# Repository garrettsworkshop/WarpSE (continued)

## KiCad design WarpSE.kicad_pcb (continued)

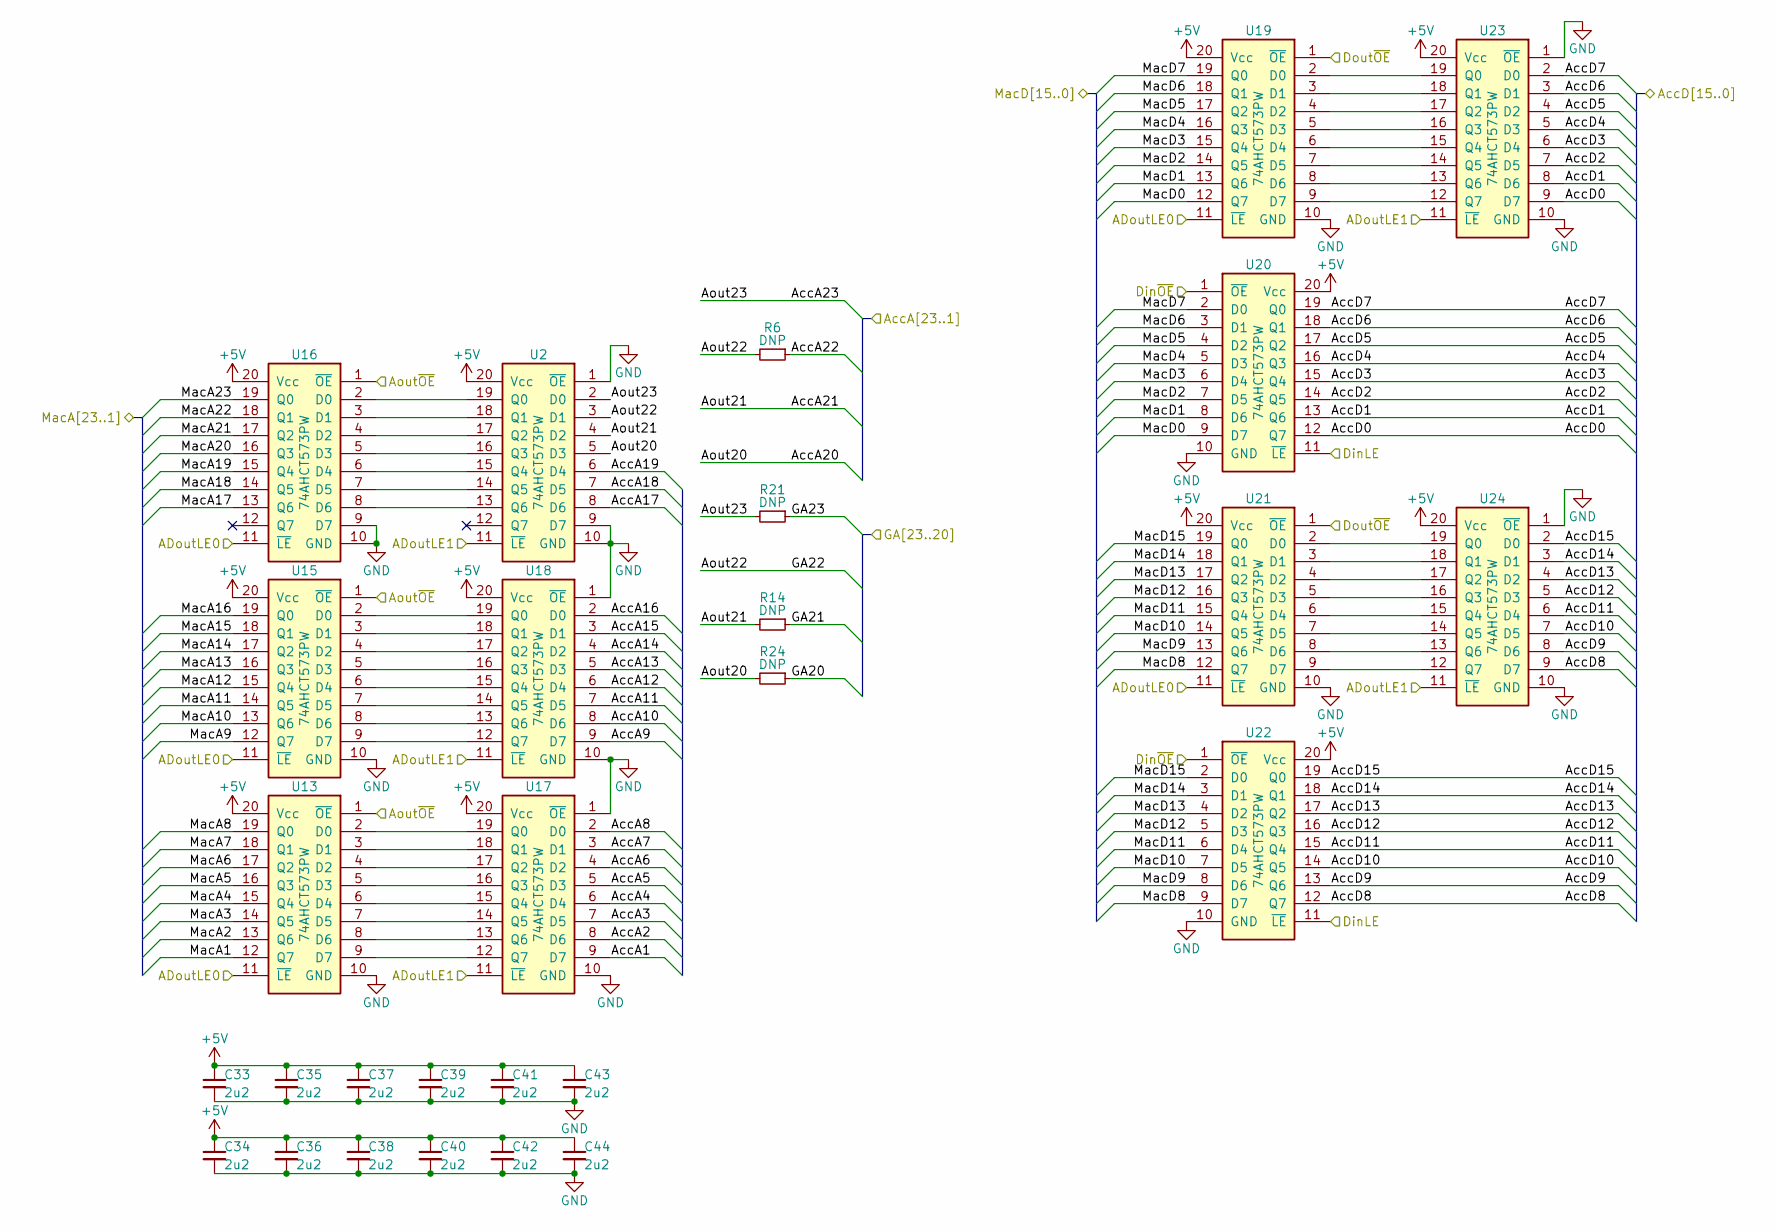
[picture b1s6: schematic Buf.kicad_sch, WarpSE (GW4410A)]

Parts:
C33, C34, C35, C36, C37, C38, C39, C40, C41, C42, C43, C44: 2u2; C_0603; LCSC Part C23630
R6, R14, R21, R24: DNP; R_0603
U2, U13, U15, U16, U17, U18, U19, U20, U21, U22, U23, U24: 74AHCT573PW; TSSOP-20_4.4x6.5mm_P0.65mm; LCSC Part C141311

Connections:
+5V: C33.1, C34.1, C35.1, C36.1, C37.1, C38.1, C39.1, C40.1, C41.1, C42.1, C43.1, C44.1, U2.20 (Vcc), U13.20 (Vcc), U15.20 (Vcc), U16.20 (Vcc), U17.20 (Vcc), U18.20 (Vcc), U19.20 (Vcc), U20.20 (Vcc), U21.20 (Vcc), U22.20 (Vcc), U23.20 (Vcc), U24.20 (Vcc); also elsewhere on the board
/Buf/ADoutLE0: U13.11 (~LE), U15.11 (~LE), U16.11 (~LE), U19.11 (~LE), U21.11 (~LE); also elsewhere on the board
/Buf/ADoutLE1: U2.11 (~LE), U17.11 (~LE), U18.11 (~LE), U23.11 (~LE), U24.11 (~LE); also elsewhere on the board
/Buf/AccA1: U17.9 (D7); also elsewhere on the board
/Buf/AccA2: U17.8 (D6); also elsewhere on the board
/Buf/AccA3: U17.7 (D5); also elsewhere on the board
/Buf/AccA4: U17.6 (D4); also elsewhere on the board
/Buf/AccA5: U17.5 (D3); also elsewhere on the board
/Buf/AccA6: U17.4 (D2); also elsewhere on the board
/Buf/AccA7: U17.3 (D1); also elsewhere on the board
/Buf/AccA8: U17.2 (D0); also elsewhere on the board
/Buf/AccA9: U18.9 (D7); also elsewhere on the board
/Buf/AccA10: U18.8 (D6); also elsewhere on the board
/Buf/AccA11: U18.7 (D5); also elsewhere on the board
/Buf/AccA12: U18.6 (D4); also elsewhere on the board
/Buf/AccA13: U18.5 (D3); also elsewhere on the board
/Buf/AccA14: U18.4 (D2); also elsewhere on the board
/Buf/AccA15: U18.3 (D1); also elsewhere on the board
/Buf/AccA16: U18.2 (D0); also elsewhere on the board
/Buf/AccA17: U2.8 (D6); also elsewhere on the board
/Buf/AccA18: U2.7 (D5); also elsewhere on the board
/Buf/AccA19: U2.6 (D4); also elsewhere on the board
/Buf/AccA20: R24.2, U2.5 (D3); also elsewhere on the board
/Buf/AccA21: R14.2, U2.4 (D2); also elsewhere on the board
/Buf/AccA22: R6.1; also elsewhere on the board
/Buf/AccA23: R21.2, U2.2 (D0); also elsewhere on the board
/Buf/AccD0: U20.12 (Q7), U23.9 (D7); also elsewhere on the board
/Buf/AccD1: U20.13 (Q6), U23.8 (D6); also elsewhere on the board
/Buf/AccD2: U20.14 (Q5), U23.7 (D5); also elsewhere on the board
/Buf/AccD3: U20.15 (Q4), U23.6 (D4); also elsewhere on the board
/Buf/AccD4: U20.16 (Q3), U23.5 (D3); also elsewhere on the board
/Buf/AccD5: U20.17 (Q2), U23.4 (D2); also elsewhere on the board
/Buf/AccD6: U20.18 (Q1), U23.3 (D1); also elsewhere on the board
/Buf/AccD7: U20.19 (Q0), U23.2 (D0); also elsewhere on the board
/Buf/AccD8: U22.12 (Q7), U24.9 (D7); also elsewhere on the board
/Buf/AccD9: U22.13 (Q6), U24.8 (D6); also elsewhere on the board
/Buf/AccD10: U22.14 (Q5), U24.7 (D5); also elsewhere on the board
/Buf/AccD11: U22.15 (Q4), U24.6 (D4); also elsewhere on the board
/Buf/AccD12: U22.16 (Q3), U24.5 (D3); also elsewhere on the board
/Buf/AccD13: U22.17 (Q2), U24.4 (D2); also elsewhere on the board
/Buf/AccD14: U22.18 (Q1), U24.3 (D1); also elsewhere on the board
/Buf/AccD15: U22.19 (Q0), U24.2 (D0); also elsewhere on the board
/Buf/Aout~OE: U13.1 (~OE), U15.1 (~OE), U16.1 (~OE); also elsewhere on the board
/Buf/DinLE: U20.11 (~LE), U22.11 (~LE); also elsewhere on the board
/Buf/Din~OE: U20.1 (~OE), U22.1 (~OE); also elsewhere on the board
/Buf/Dout~OE: U19.1 (~OE), U21.1 (~OE); also elsewhere on the board
/Buf/GA20: R24.1; also elsewhere on the board
/Buf/GA21: R14.1; also elsewhere on the board
/Buf/GA22: R6.2, U2.3 (D1); also elsewhere on the board
/Buf/GA23: R21.1; also elsewhere on the board
/Buf/MacA1: U13.12 (Q7); also elsewhere on the board
/Buf/MacA2: U13.13 (Q6); also elsewhere on the board
/Buf/MacA3: U13.14 (Q5); also elsewhere on the board
/Buf/MacA4: U13.15 (Q4); also elsewhere on the board
/Buf/MacA5: U13.16 (Q3); also elsewhere on the board
/Buf/MacA6: U13.17 (Q2); also elsewhere on the board
/Buf/MacA7: U13.18 (Q1); also elsewhere on the board
/Buf/MacA8: U13.19 (Q0); also elsewhere on the board
/Buf/MacA9: U15.12 (Q7); also elsewhere on the board
/Buf/MacA10: U15.13 (Q6); also elsewhere on the board
/Buf/MacA11: U15.14 (Q5); also elsewhere on the board
/Buf/MacA12: U15.15 (Q4); also elsewhere on the board
/Buf/MacA13: U15.16 (Q3); also elsewhere on the board
/Buf/MacA14: U15.17 (Q2); also elsewhere on the board
/Buf/MacA15: U15.18 (Q1); also elsewhere on the board
/Buf/MacA16: U15.19 (Q0); also elsewhere on the board
/Buf/MacA17: U16.13 (Q6); also elsewhere on the board
/Buf/MacA18: U16.14 (Q5); also elsewhere on the board
/Buf/MacA19: U16.15 (Q4); also elsewhere on the board
/Buf/MacA20: U16.16 (Q3); also elsewhere on the board
/Buf/MacA21: U16.17 (Q2); also elsewhere on the board
/Buf/MacA22: U16.18 (Q1); also elsewhere on the board
/Buf/MacA23: U16.19 (Q0); also elsewhere on the board
/Buf/MacD0: U19.12 (Q7), U20.9 (D7); also elsewhere on the board
/Buf/MacD1: U19.13 (Q6), U20.8 (D6); also elsewhere on the board
/Buf/MacD2: U19.14 (Q5), U20.7 (D5); also elsewhere on the board
/Buf/MacD3: U19.15 (Q4), U20.6 (D4); also elsewhere on the board
/Buf/MacD4: U19.16 (Q3), U20.5 (D3); also elsewhere on the board
/Buf/MacD5: U19.17 (Q2), U20.4 (D2); also elsewhere on the board
/Buf/MacD6: U19.18 (Q1), U20.3 (D1); also elsewhere on the board
/Buf/MacD7: U19.19 (Q0), U20.2 (D0); also elsewhere on the board
/Buf/MacD8: U21.12 (Q7), U22.9 (D7); also elsewhere on the board
/Buf/MacD9: U21.13 (Q6), U22.8 (D6); also elsewhere on the board
/Buf/MacD10: U21.14 (Q5), U22.7 (D5); also elsewhere on the board
/Buf/MacD11: U21.15 (Q4), U22.6 (D4); also elsewhere on the board
/Buf/MacD12: U21.16 (Q3), U22.5 (D3); also elsewhere on the board
/Buf/MacD13: U21.17 (Q2), U22.4 (D2); also elsewhere on the board
/Buf/MacD14: U21.18 (Q1), U22.3 (D1); also elsewhere on the board
/Buf/MacD15: U21.19 (Q0), U22.2 (D0); also elsewhere on the board
GND: C33.2, C34.2, C35.2, C36.2, C37.2, C38.2, C39.2, C40.2, C41.2, C42.2, C43.2, C44.2, U2.1 (~OE), U2.9 (D7), U2.10 (GND), U13.10 (GND), U15.10 (GND), U16.9 (D7), U16.10 (GND), U17.1 (~OE), U17.10 (GND), U18.1 (~OE), U18.10 (GND), U19.10 (GND), U20.10 (GND), U21.10 (GND), U22.10 (GND), U23.1 (~OE), U23.10 (GND), U24.1 (~OE), U24.10 (GND); also elsewhere on the board
unnamed: U13.2 (D0), U17.19 (Q0)
unnamed: U13.3 (D1), U17.18 (Q1)
unnamed: U13.4 (D2), U17.17 (Q2)
unnamed: U13.5 (D3), U17.16 (Q3)
unnamed: U13.6 (D4), U17.15 (Q4)
unnamed: U13.7 (D5), U17.14 (Q5)
unnamed: U13.8 (D6), U17.13 (Q6)
unnamed: U13.9 (D7), U17.12 (Q7)
unnamed: U15.2 (D0), U18.19 (Q0)
unnamed: U15.3 (D1), U18.18 (Q1)
unnamed: U15.4 (D2), U18.17 (Q2)
unnamed: U15.5 (D3), U18.16 (Q3)
unnamed: U15.6 (D4), U18.15 (Q4)
unnamed: U15.7 (D5), U18.14 (Q5)
unnamed: U15.8 (D6), U18.13 (Q6)
unnamed: U15.9 (D7), U18.12 (Q7)
unnamed: U2.19 (Q0), U16.2 (D0)
unnamed: U2.18 (Q1), U16.3 (D1)
unnamed: U2.17 (Q2), U16.4 (D2)
unnamed: U2.16 (Q3), U16.5 (D3)
unnamed: U2.15 (Q4), U16.6 (D4)
unnamed: U2.14 (Q5), U16.7 (D5)
unnamed: U2.13 (Q6), U16.8 (D6)
unnamed: U19.2 (D0), U23.19 (Q0)
unnamed: U19.3 (D1), U23.18 (Q1)
unnamed: U19.4 (D2), U23.17 (Q2)
unnamed: U19.5 (D3), U23.16 (Q3)
unnamed: U19.6 (D4), U23.15 (Q4)
unnamed: U19.7 (D5), U23.14 (Q5)
unnamed: U19.8 (D6), U23.13 (Q6)
unnamed: U19.9 (D7), U23.12 (Q7)
unnamed: U21.2 (D0), U24.19 (Q0)
unnamed: U21.3 (D1), U24.18 (Q1)
unnamed: U21.4 (D2), U24.17 (Q2)
unnamed: U21.5 (D3), U24.16 (Q3)
unnamed: U21.6 (D4), U24.15 (Q4)
unnamed: U21.7 (D5), U24.14 (Q5)
unnamed: U21.8 (D6), U24.13 (Q6)
unnamed: U21.9 (D7), U24.12 (Q7)

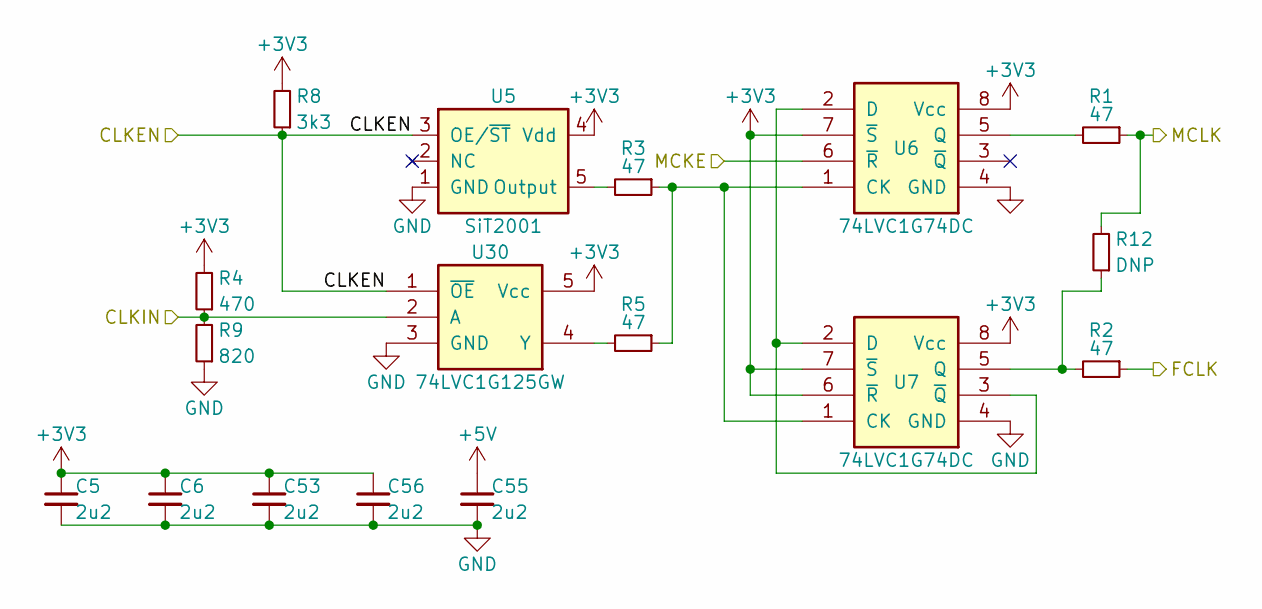
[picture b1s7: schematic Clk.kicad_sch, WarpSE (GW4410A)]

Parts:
C5, C6, C53, C55, C56: 2u2; C_0603; LCSC Part C23630
R1, R2, R3, R5: 47; R_0603; LCSC Part C23182
R4: 470; R_0603; LCSC Part C21190
R8: 3k3; R_0603; LCSC Part C21190
R9: 820; R_0603; LCSC Part C21190
R12: DNP; R_0603
U5: SiT2001; SOT-23-5; LCSC Part C17253174
U6, U7: 74LVC1G74DC; NXP_VSSOP-8_2.3x2mm; LCSC Part C503431
U30: 74LVC1G125GW; SOT-353; LCSC Part C12519

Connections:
+3V3: C5.1, C6.1, C53.1, C56.1, R4.2, R8.2, U5.4 (Vdd), U6.7 (~S), U6.8 (Vcc), U7.6 (~R), U7.7 (~S), U7.8 (Vcc), U30.5 (Vcc); also elsewhere on the board
+5V: C55.1; also elsewhere on the board
/Clk.sch/CLKEN: R8.1, U5.3 (OE/~ST), U30.1 (~OE); also elsewhere on the board
/Clk.sch/CLKIN: R4.1, R9.2, U30.2 (A); also elsewhere on the board
/Clk.sch/FCLK: R2.1; also elsewhere on the board
/Clk.sch/MCKE: U6.6 (~R); also elsewhere on the board
/Clk.sch/MCLK: R1.1, R12.2; also elsewhere on the board
GND: C5.2, C6.2, C53.2, C55.2, C56.2, R9.1, U5.1 (GND), U6.4 (GND), U7.4 (GND), U30.3 (GND); also elsewhere on the board
unnamed: R3.2, U5.5 (Output)
unnamed: R3.1, R5.1, U6.1 (CK), U7.1 (CK)
unnamed: U6.2 (D), U7.2 (D), U7.3 (~Q)
unnamed: R1.2, U6.5 (Q)
unnamed: R2.2, R12.1, U7.5 (Q)
unnamed: R5.2, U30.4 (Y)

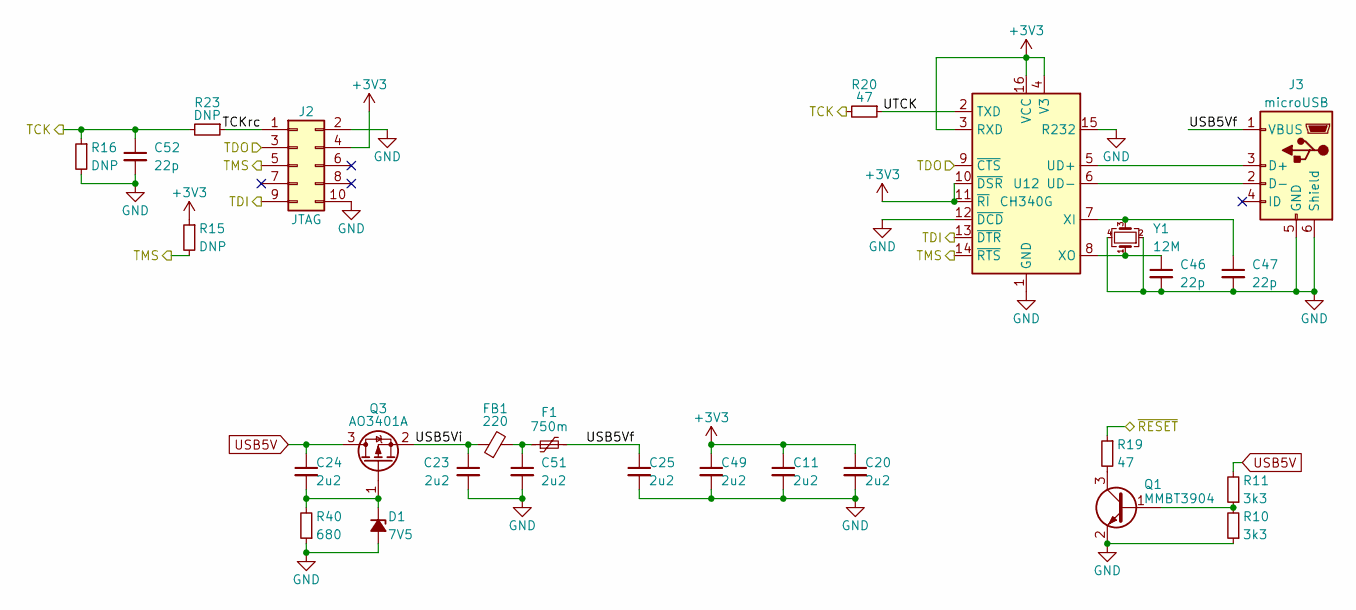
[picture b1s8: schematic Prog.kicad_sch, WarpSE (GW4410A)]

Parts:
C11, C20, C23, C24, C25, C49, C51: 2u2; C_0603; LCSC Part C23630
C46, C47, C52: 22p; C_0603; LCSC Part C1653
D1: 7V5; D_SOD-323; LCSC Part C95638
F1: 750m; BelFuse_1206; LCSC Part C126818
FB1: 220; C_0805; LCSC Part C85840
J2: JTAG; Tag-Connect_TC2050-IDC-FP_2x05_P1.27mm_Vertical
J3: microUSB; USB_Micro-B_Amphenol_10118192-0001; LCSC Part C132564
Q1: MMBT3904; SOT-23; LCSC Part C20526
Q3: AO3401A; SOT-23
R10, R11: 3k3; R_0603; LCSC Part C21190
R15, R16, R23: DNP; R_0603
R19, R20: 47; R_0603; LCSC Part C23182
R40: 680; R_0805; LCSC Part C17798
U12: CH340G; SOIC-16_3.9mm; LCSC Part C14267
Y1: 12M; Crystal_SMD_3225-4Pin_3.2x2.5mm; LCSC Part C9002

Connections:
+3V3: C11.1, C20.1, C49.1, J2.4, R15.1, U12.3 (RXD), U12.4 (V3), U12.10 (~DSR), U12.11 (~RI), U12.16 (VCC); also elsewhere on the board
/Control/TCK: C52.1, R16.1, R20.2, R23.2; also elsewhere on the board
/Control/TDI: J2.9, U12.13 (~DTR); also elsewhere on the board
/Control/TDO: J2.3, U12.9 (~CTS); also elsewhere on the board
/Control/TMS: J2.5, R15.2, U12.14 (~RTS); also elsewhere on the board
/Control/~RESET: R19.1; also elsewhere on the board
/Prog/TCKrc: J2.1, R23.1
/Prog/USB5Vf: C25.1, F1.2, J3.1 (VBUS)
/Prog/USB5Vi: C23.1, FB1.1, Q3.2 (S)
/Prog/UTCK: R20.1, U12.2 (TXD)
GND: C11.2, C20.2, C23.2, C25.2, C46.2, C47.2, C49.2, C51.2, C52.2, D1.2 (A), J2.2, J2.10, J3.5 (GND), J3.6 (Shield), Q1.2 (E), R10.1, R16.2, R40.1, U12.1 (GND), U12.12 (~DCD), U12.15 (R232), Y1.2, Y1.4; also elsewhere on the board
unnamed: C51.1, F1.1, FB1.2
unnamed: C24.2, D1.1 (K), Q3.1 (G), R40.2
unnamed: J3.3 (D+), U12.5 (UD+)
unnamed: J3.2 (D-), U12.6 (UD-)
unnamed: Q1.1 (B), R10.2, R11.1
unnamed: Q1.3 (C), R19.2
unnamed: C47.1, U12.7 (XI), Y1.3
unnamed: C46.1, U12.8 (XO), Y1.1
USB5V: C24.1, Q3.3 (D), R11.2; also elsewhere on the board

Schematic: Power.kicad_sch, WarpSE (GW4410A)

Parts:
C3, C4, C7, C8, C9, C10: 10u; C_0805; LCSC Part C15850
C19, C45, C50: 2u2; C_0603; LCSC Part C23630
Q2: DNP; SOT-23
R25, R26, R27: 680; R_0805; LCSC Part C17798
R28: DNP; R_0805
R37: 3k3; R_0603; LCSC Part C21190
U3: AZ1117CH-3.3TRG1; SOT-223; LCSC Part C92102
U4, U25: LM66100DCK; SOT-363; LCSC Part C2869734

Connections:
+3V3: C7.1, C8.1, C9.1, C10.1, R26.1, R28.1, U3.2 (VO); also elsewhere on the board
+5V: C3.1, C4.1, C19.1, C45.1, Q2.2 (E), R25.1, U3.3 (VI), U4.6 (Vout), U25.6 (Vout); also elsewhere on the board
+5Vin: R27.1, R37.2, U25.1 (Vin); also elsewhere on the board
GND: C3.2, C4.2, C7.2, C8.2, C9.2, C10.2, C19.2, C45.2, C50.2, R25.2, R26.2, R27.2, U3.1 (GND), U4.2 (GND), U25.2 (GND); also elsewhere on the board
unnamed: Q2.1 (B), Q2.3 (C), R28.2
unnamed: R37.1, U4.3 (~CE), U25.5 (ST)
USB5V: C50.1, U4.1 (Vin), U25.3 (~CE); also elsewhere on the board

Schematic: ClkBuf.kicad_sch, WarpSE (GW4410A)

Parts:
C21, C48, C54: 2u2; C_0603; LCSC Part C23630
R7, R17, R18: 47; R_0603; LCSC Part C23182
R29: 22k; R_0805; LCSC Part C17560
U26, U27, U28: 74LVC1G32GW; SOT-353; LCSC Part C12516

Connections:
+3V3: C21.1, C48.1, C54.1, U26.5 (Vcc), U27.5 (Vcc), U28.5 (Vcc); also elsewhere on the board
+5Vin: R29.1; also elsewhere on the board
/ClkBuf/BC8M: R17.1; also elsewhere on the board
/ClkBuf/BC16M: R7.1; also elsewhere on the board
/ClkBuf/BE: R18.1; also elsewhere on the board
/ClkBuf/C8M: R29.2, U27.2 (B); also elsewhere on the board
/ClkBuf/C16M: U28.2 (B); also elsewhere on the board
/ClkBuf/E: U26.2 (B); also elsewhere on the board
GND: C21.2, C48.2, C54.2, U26.1 (A), U26.3 (GND), U27.1 (A), U27.3 (GND), U28.1 (A), U28.3 (GND); also elsewhere on the board
unnamed: R18.2, U26.4 (Y)
unnamed: R17.2, U27.4 (Y)
unnamed: R7.2, U28.4 (Y)

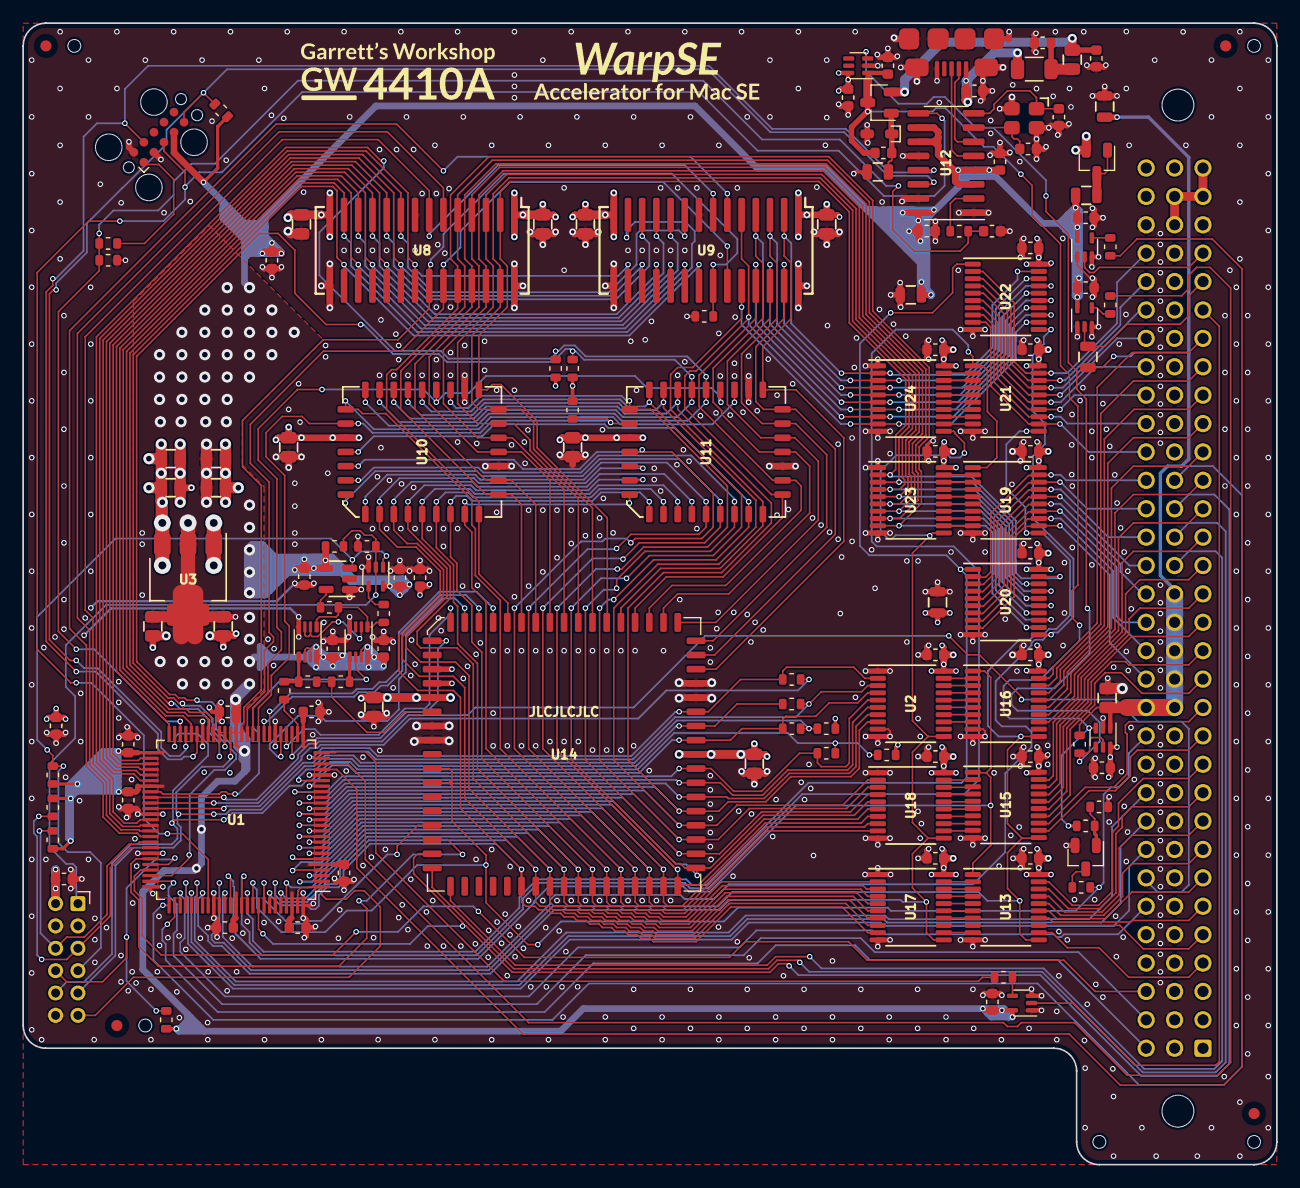
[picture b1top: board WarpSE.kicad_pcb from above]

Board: 4 copper layers, 112.1 x 102.1 mm, 144 parts (0 on the bottom side), 215 nets.

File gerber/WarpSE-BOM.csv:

"Reference","Quantity","Value","Footprint","LCSC Part","DNP"
"C1, C2, C3, C4, C7, C8, C9, C10, C12, C13, C14, C15, C16, C17, C18","15","10u","stdpads:C_0805","C15850",""
"C5, C6, C11, C19, C20, C21, C22, C23, C24, C25, C26, C27, C28, C29, C30, C31, C32, C33, C34, C35, C36, C37, C38, C39, C40, C41, C42, C43, C44, C45, C48, C49, C50, C51, C53, C54, C55, C56, C57","39","2u2","stdpads:C_0603","C23630",""
"C46, C47, C52","3","22p","stdpads:C_0603","C1653",""
"D1","1","7V5","stdpads:D_SOD-323","C95638",""
"F1","1","750m","stdpads:BelFuse_1206","C126818",""
"FB1","1","220","stdpads:C_0805","C85840",""
"FID1, FID2, FID3, FID4","4","Fiducial","stdpads:Fiducial","",""
"H1, H2, H3, H4, H5","5","~","stdpads:PasteHole_1.152mm_NPTH","",""
"J1","1","MacSEPDS","stdpads:DIN41612_R_3x32_Male_Vertical_THT","",""
"J2","1","JTAG","stdpads:Tag-Connect_TC2050-IDC-FP_2x05_P1.27mm_Vertical","",""
"J3","1","microUSB","stdpads:USB_Micro-B_Amphenol_10118192-0001","C132564",""
"J4","1","DBG","stdpads:PinSocket_2x06_P2.00mm_Vertical","",""
"Q1","1","MMBT3904","stdpads:SOT-23","C20526",""
"Q2","1","DNP","stdpads:SOT-23","",""
"Q3","1","AO3401A","stdpads:SOT-23","",""
"R1, R2, R3, R5, R7, R17, R18, R19, R20","9","47","stdpads:R_0603","C23182",""
"R4","1","470","stdpads:R_0603","C21190",""
"R6, R12, R14, R15, R16, R21, R23, R24, R30, R35, R36","11","DNP","stdpads:R_0603","",""
"R8, R10, R11, R31, R32, R33, R34, R37, R38, R39","10","3k3","stdpads:R_0603","C21190",""
"R9","1","820","stdpads:R_0603","C21190",""
"R25, R26, R27, R40","4","680","stdpads:R_0805","C17798",""
"R28","1","DNP","stdpads:R_0805","",""
"R29","1","22k","stdpads:R_0805","C17560",""
"U1","1","XC95144XL-TQ100","stdpads:TQFP-100_14x14mm_P0.5mm","C45126",""
"U2, U13, U15, U16, U17, U18, U19, U20, U21, U22, U23, U24","12","74AHCT573PW","stdpads:TSSOP-20_4.4x6.5mm_P0.65mm","C141311",""
"U3","1","AZ1117CH-3.3TRG1","stdpads:SOT-223","C92102",""
"U4, U25","2","LM66100DCK","stdpads:SOT-363","C2869734",""
"U5","1","SiT2001","stdpads:SOT-23-5","C17253174",""
"U6, U7","2","74LVC1G74DC","stdpads:NXP_VSSOP-8_2.3x2mm","C503431",""
"U8, U9","2","KM48C2100","stdpads:SOJ-28_300mil","",""
"U10, U11","2","39SF040","stdpads:PLCC-32","C645935",""
"U12","1","CH340G","stdpads:SOIC-16_3.9mm","C14267",""
"U14","1","MC68HC000FN20","stdpads:PLCC-68","",""
"U26, U27, U28","3","74LVC1G32GW","stdpads:SOT-353","C12516",""
"U30","1","74LVC1G125GW","stdpads:SOT-353","C12519",""
"Y1","1","12M","stdpads:Crystal_SMD_3225-4Pin_3.2x2.5mm","C9002",""

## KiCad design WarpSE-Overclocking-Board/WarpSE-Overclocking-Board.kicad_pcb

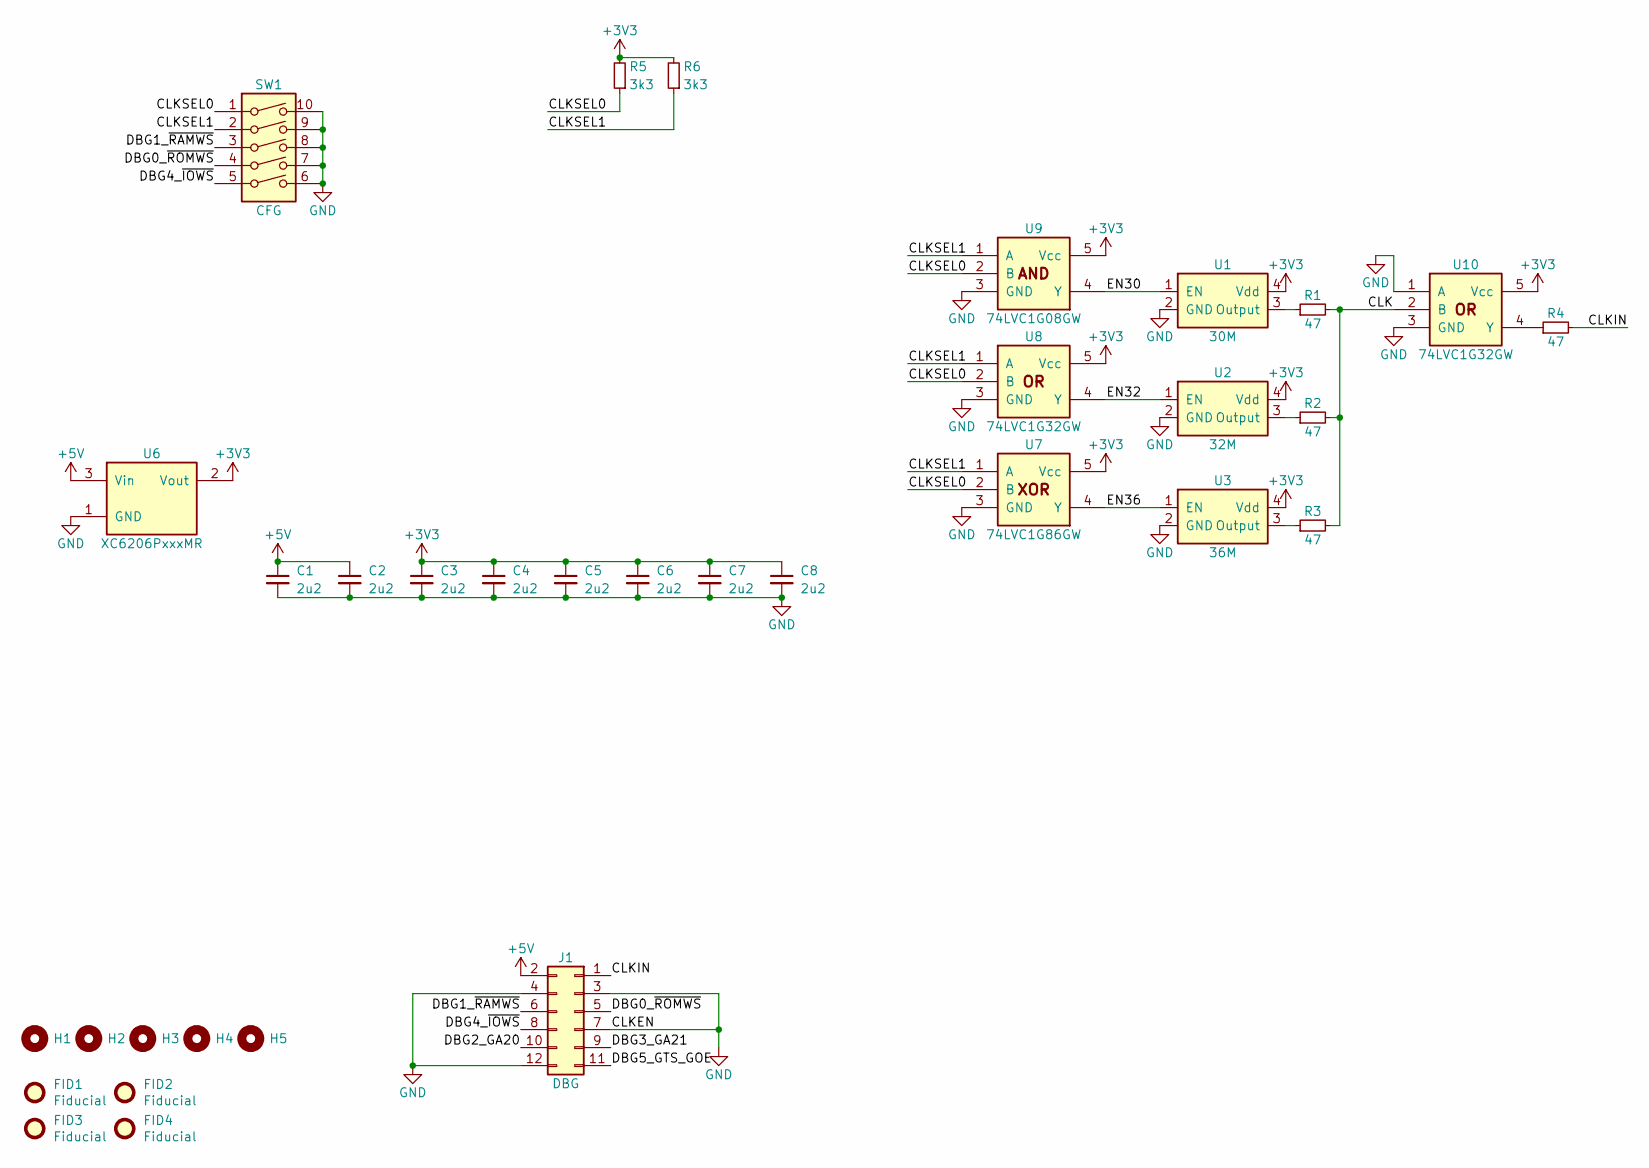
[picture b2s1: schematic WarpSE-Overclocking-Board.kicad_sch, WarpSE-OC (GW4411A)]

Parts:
C1, C2, C3, C4, C5, C6, C7, C8: 2u2; C_0603
FID1, FID2, FID3, FID4: Fiducial
H1, H2, H3, H4, H5: PasteHole_1.152mm_NPTH
J1: DBG; PinHeader_2x06_P2.54mm_Vertical
R1, R2, R3, R4: 47; R_0603
R5, R6: 3k3; R_0603
SW1: CFG; SW_DIP_SPSTx05_Slide_DSHP05TS_P1.27mm
U1: 30M; Crystal_SMD_3225-4Pin_3.2x2.5mm
U2: 32M; Crystal_SMD_3225-4Pin_3.2x2.5mm
U3: 36M; Crystal_SMD_3225-4Pin_3.2x2.5mm
U6: XC6206PxxxMR; SOT-23
U7: 74LVC1G86GW; SOT-353
U8, U10: 74LVC1G32GW; SOT-353
U9: 74LVC1G08GW; SOT-353

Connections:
+3V3: C3.1, C4.1, C5.1, C6.1, C7.1, C8.1, R5.2, R6.2, U1.4 (Vdd), U2.4 (Vdd), U3.4 (Vdd), U6.2 (Vout), U7.5 (Vcc), U8.5 (Vcc), U9.5 (Vcc), U10.5 (Vcc)
+5V: C1.1, C2.1, J1.2, U6.3 (Vin)
/CLK: R1.2, R2.2, R3.2, U10.2 (B)
/CLKIN: J1.1, R4.2
/CLKSEL0: R5.1, SW1.1, U7.2 (B), U8.2 (B), U9.2 (B)
/CLKSEL1: R6.1, SW1.2, U7.1 (A), U8.1 (A), U9.1 (A)
/DBG0_~ROMWS: J1.5, SW1.4
/DBG1_~RAMWS: J1.6, SW1.3
/DBG2_GA20: J1.10
/DBG3_GA21: J1.9
/DBG4_~IOWS: J1.8, SW1.5
/DBG5_GTS_GOE: J1.11
/EN30: U1.1 (EN), U9.4 (Y)
/EN32: U2.1 (EN), U8.4 (Y)
/EN36: U3.1 (EN), U7.4 (Y)
GND: C1.2, C2.2, C3.2, C4.2, C5.2, C6.2, C7.2, C8.2, J1.3, J1.4, J1.7, J1.12, SW1.6, SW1.7, SW1.8, SW1.9, SW1.10, U1.2 (GND), U2.2 (GND), U3.2 (GND), U6.1 (GND), U7.3 (GND), U8.3 (GND), U9.3 (GND), U10.1 (A), U10.3 (GND)
unnamed: R1.1, U1.3 (Output)
unnamed: R2.1, U2.3 (Output)
unnamed: R3.1, U3.3 (Output)
unnamed: R4.1, U10.4 (Y)

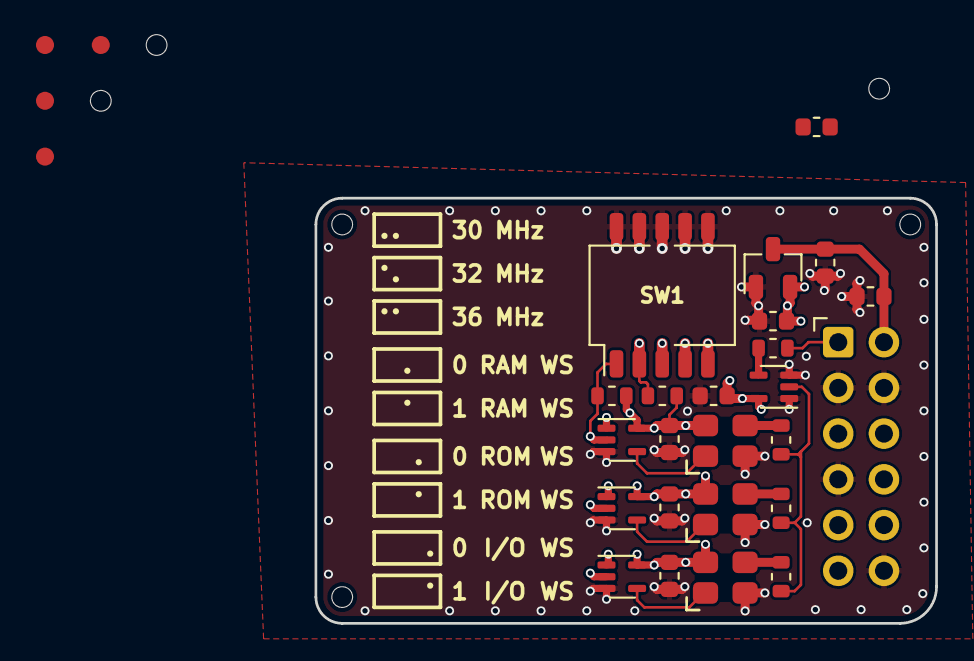
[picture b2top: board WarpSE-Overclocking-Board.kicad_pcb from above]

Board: 4 copper layers, 34.5 x 23.6 mm, 34 parts (0 on the bottom side), 17 nets.

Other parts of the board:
H3#2: PasteHole_1.152mm_NPTH

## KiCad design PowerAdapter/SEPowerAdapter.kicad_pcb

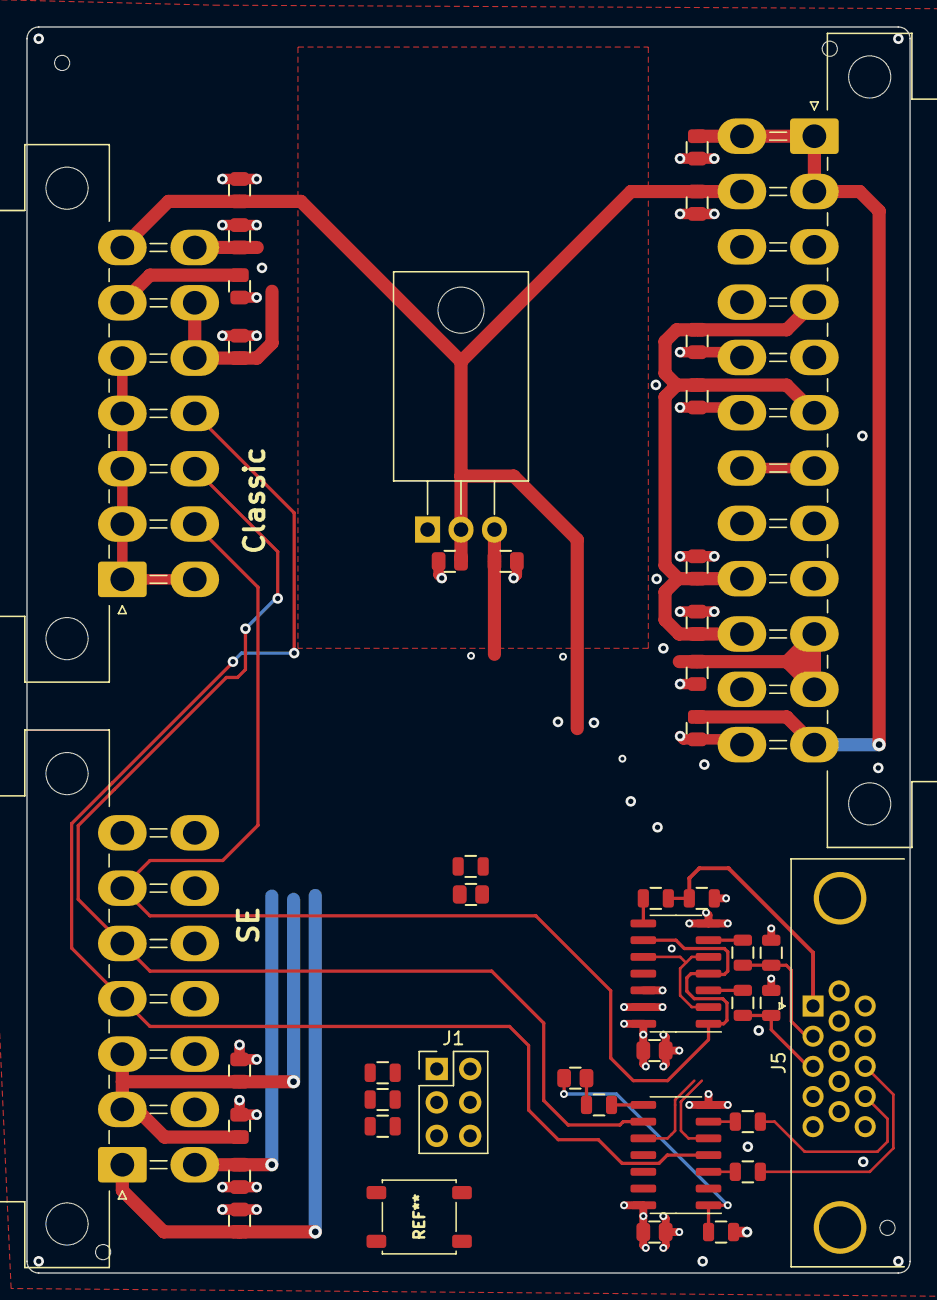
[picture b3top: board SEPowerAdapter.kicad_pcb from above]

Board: 4 copper layers, 67.1 x 94.6 mm, 44 parts (0 on the bottom side), 27 nets.

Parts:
C1, C2, C3, C4, C5, C6, C7, C8, C9, C10, C11, C12, C13, C14, C15, C16, C18, C19, C20, C22, C23: 10u; C_0805
C17: 1n; C_0805
J1: XOR; PinHeader_2x03_P2.54mm_Vertical
J2: ATX; Molex_Mini-Fit_Jr_5569-24A1_2x12_P4.20mm_Horizontal
J3: SE; Molex_Mini-Fit_Jr_5569-14A1_2x07_P4.20mm_Horizontal
J4: Classic; Molex_Mini-Fit_Jr_5569-14A1_2x07_P4.20mm_Horizontal
J5: VGA; DSUB-15-HD_Female_Horizontal_P2.29x1.98mm_EdgePinOffset3.03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
R1, R2, R3, R13: 2k2; R_0805
R4, R5, R12: 47; R_0805
R6, R8, R10: 150; R_0805
R7, R9, R11: 130; R_0805
R14: 22k; R_0805
U1: LM7905_TO220; TO-220-3_Horizontal_TabDown
U2, U3: 74LVC86AD; SOIC-14_3.9mm

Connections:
+3V3: C8.1, C9.1, C10.1, C16.1, J2.1, J2.2, J2.12, J2.13, R1.2, R2.2, R3.2, U2.14 (VCC), U3.14 (VCC)
+5V: C3.1, C4.1, C5.1, C6.1, C7.1, C22.1, C23.1, J2.4, J2.6, J2.21, J2.22, J2.23, J3.12, J3.13, J4.2, J4.3, R13.1
+5VP: J2.9, R14.1
+12V: C1.1, C2.1, C19.1, J2.10, J2.11, J3.14, J4.1
-5V: C14.2, C15.2, J3.6, U1.3 (VO)
-12V: C11.2, C12.2, C13.2, C20.2, J2.14, J3.7, J4.8, U1.2 (VI)
/Bo: J5.3, R10.2, R11.2
/Ci: J3.9, J4.6, U3.1, U3.4, U3.9
/Cx: J1.5, R1.1, U3.2, U3.5, U3.10
/Go: J5.2, R8.2, R9.2
/HSf: C17.2, R13.2, U2.1
/HSi: J3.10, J4.5, U2.9
/HSo: J5.13, R4.2
/HSx: J1.3, R2.1, U2.10
/Ro: J5.1, R6.2, R7.2
/VSi: J3.11, J4.4, U2.4
/VSo: J5.14, R5.2
/VSx: J1.1, R3.1, U2.5
/~POR: C18.1, R14.2
GND: C1.2, C2.2, C3.2, C4.2, C5.2, C6.2, C7.2, C8.2, C9.2, C10.2, C11.1, C12.1, C13.1, C14.1, C15.1, C16.2, C18.2, C19.2, C20.1, C22.2, C23.2, J1.2, J1.4, J1.6, J2.3, J2.5, J2.7, J2.15, J2.17, J2.18, J2.19, J2.24, J3.1, J3.2, J3.3, J3.4, J3.5, J3.8, J4.10, J4.11, J4.12, J4.13, J4.14, J5.0, J5.5, J5.6, J5.7, J5.8, J5.10, R7.1, R9.1, R11.1, U1.1 (GND), U2.2, U2.7 (GND), U2.12, U2.13, U3.7 (GND), U3.12, U3.13
unnamed: C17.1, R12.2
unnamed: R4.1, U2.3
unnamed: R5.1, U2.6
unnamed: R6.1, U3.8
unnamed: R8.1, U3.6
unnamed: R10.1, U3.3
unnamed: R12.1, U2.8

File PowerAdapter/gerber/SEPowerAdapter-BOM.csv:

"Source:","/Users/zane/Library/Mobile Documents/com~apple~CloudDocs/Repos/Warp-SE/PowerAdapter/SEPowerAdapter.kicad_sch"
"Date:","Wednesday, April 20, 2022 at 05:56:59 AM"
"Tool:","Eeschema (6.0.2-0)"
"Generator:","/Applications/KiCad/KiCad.app/Contents/SharedSupport/plugins/bom_jlc.py"
"Component Count:","34"
"Ref","Qnty","Value","Cmp name","Footprint","Description","Vendor","LCSC Part"
"C1, C2, C3, C4, C5, C6, C7, C8, C9, C10, C11, C12, C13, C14, C15, C16, ","16","10u","C_Small","stdpads:C_0805","Unpolarized capacitor, small symbol","","C15850"
"J1, ","1","XOR","Conn_02x03_Odd_Even","Connector_PinHeader_2.54mm:PinHeader_2x03_P2.54mm_Vertical","Generic connector, double row, 02x03, odd/even pin numbering scheme (row 1 odd numbers, row 2 even numbers), script generated (kicad-library-utils/schlib/autogen/connector/)","","C65114"
"J2, ","1","ATX","Conn_02x12_Top_Bottom","Connector_Molex:Molex_Mini-Fit_Jr_5569-24A1_2x12_P4.20mm_Horizontal","Generic connector, double row, 02x12, top/bottom pin numbering scheme (row 1: 1...pins_per_row, row2: pins_per_row+1 ... num_pins), script generated (kicad-library-utils/schlib/autogen/connector/)","","C477841"
"J3, ","1","Mac","Conn_02x07_Top_Bottom","Connector_Molex:Molex_Mini-Fit_Jr_5569-14A1_2x07_P4.20mm_Horizontal","Generic connector, double row, 02x07, top/bottom pin numbering scheme (row 1: 1...pins_per_row, row2: pins_per_row+1 ... num_pins), script generated (kicad-library-utils/schlib/autogen/connector/)","","C52216"
"J4, ","1","VGA","DB15_Female_HighDensity_MountingHoles","Connector_Dsub:DSUB-15-HD_Female_Horizontal_P2.29x1.98mm_EdgePinOffset3.03mm_Housed_MountingHolesOffset4.94mm","15-pin female D-SUB connector, High density (3 columns), Triple Row, Generic, VGA-connector, Mounting Hole","","C75754"
"R1, R2, R3, ","3","1k","R_Small","stdpads:R_0805","Resistor, small symbol","","C17513"
"R4, R5, ","2","47","R_Small","stdpads:R_0805","Resistor, small symbol","","C17714"
"R6, R8, R10, ","3","150","R_Small","stdpads:R_0805","Resistor, small symbol","","C17471"
"R7, R9, R11, ","3","130","R_Small","stdpads:R_0805","Resistor, small symbol","","C17437"
"U1, ","1","LM7905_TO220","LM7905_TO220","Package_TO_SOT_THT:TO-220-3_Horizontal_TabDown","Negative 1A 35V Linear Regulator, Fixed Output 5V, TO-220","","C9411"
"U2, U3, ","2","74LVC86AD","74LS86","stdpads:SOIC-14_3.9mm","Quad 2-input XOR","","C548853"

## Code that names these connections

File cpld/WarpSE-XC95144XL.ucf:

NET "A_FSB<10>"  LOC = "P8"  ; 
NET "A_FSB<11>"  LOC = "P9"  ; 
NET "A_FSB<12>"  LOC = "P10"  ; 
NET "A_FSB<13>"  LOC = "P11"  ; 
NET "A_FSB<14>"  LOC = "P12"  ; 
NET "A_FSB<15>"  LOC = "P13"  ; 
NET "A_FSB<16>"  LOC = "P14"  ; 
NET "A_FSB<17>"  LOC = "P15"  ; 
NET "A_FSB<18>"  LOC = "P16"  ; 
NET "A_FSB<19>"  LOC = "P17"  ; 
NET "A_FSB<1>"  LOC = "P94"  ; 
NET "A_FSB<20>"  LOC = "P18"  ; 
NET "A_FSB<21>"  LOC = "P19"  ; 
NET "A_FSB<22>"  LOC = "P20"  ; 
NET "A_FSB<23>"  LOC = "P24"  ; 
NET "A_FSB<2>"  LOC = "P95"  ; 
NET "A_FSB<3>"  LOC = "P96"  ; 
NET "A_FSB<4>"  LOC = "P97"  ; 
NET "A_FSB<5>"  LOC = "P2"  ; 
NET "A_FSB<6>"  LOC = "P3"  ; 
NET "A_FSB<7>"  LOC = "P4"  ; 
NET "A_FSB<8>"  LOC = "P6"  ; 
NET "A_FSB<9>"  LOC = "P7"  ; 
NET "MCKE"  LOC = "P58"  ; 
NET "FCLK"  LOC = "P27"  ; 
NET "C16M"  LOC = "P22"  ; 
NET "C8M"  LOC = "P23"  ; 
NET "E"  LOC = "P25"  ; 
NET "nADoutLE0"  LOC = "P85" | SLEW = SLOW  ; 
NET "nADoutLE1"  LOC = "P82"  ; 
NET "nAoutOE"  LOC = "P87" | SLEW = SLOW  ; 
NET "nAS_FSB"  LOC = "P32"  ; 
NET "nAS_IOB"  LOC = "P81" | SLEW = SLOW  ; 
NET "nBERR_FSB"  LOC = "P70" | SLEW = SLOW  ; 
NET "nBERR_IOB"  LOC = "P76"  ; 
NET "nBG_IOB"  LOC = "P73"  ;
NET "nBR_IOB"  LOC = "P72" | SLEW=SLOW  ;
NET "nCAS"  LOC = "P36"  ; 
NET "nDinLE"  LOC = "P86"  ; 
NET "nDinOE"  LOC = "P90" | SLEW = SLOW  ; 
NET "nDoutOE"  LOC = "P89"  ; 
NET "nDTACK_FSB"  LOC = "P28" | SLEW = SLOW  ; 
NET "nDTACK_IOB"  LOC = "P78"  ; 
NET "nIPL2"  LOC = "P92"  ;
NET "nLDS_FSB"  LOC = "P30"  ; 
NET "nLDS_IOB"  LOC = "P79" | SLEW=SLOW  ; 
NET "nOE"  LOC = "P37" | SLEW = SLOW  ; 
NET "nRAMLWE"  LOC = "P65" | SLEW = SLOW  ; 
NET "nRAMUWE"  LOC = "P66" | SLEW = SLOW  ; 
NET "nRAS"  LOC = "P64"  ; 
NET "nRES"  LOC = "P91" | SLEW=SLOW  ; 
NET "nROMOE"  LOC = "P35" | SLEW = SLOW  ; 
NET "nROMWE"  LOC = "P34" | SLEW = SLOW  ; 
NET "nUDS_FSB"  LOC = "P33"  ; 
NET "nUDS_IOB"  LOC = "P80" | SLEW=SLOW  ; 
NET "nVMA_IOB"  LOC = "P74" | SLEW=SLOW  ; 
NET "nVPA_FSB"  LOC = "P93" | SLEW = SLOW  ; 
NET "nVPA_IOB"  LOC = "P77"  ; 
NET "nWE_FSB"  LOC = "P29"  ; 
NET "RA<0>"  LOC = "P53"  ; 
NET "RA<10>"  LOC = "P55"  ; 
NET "RA<11>"  LOC = "P63"  ; 
NET "RA<1>"  LOC = "P50"  ; 
NET "RA<2>"  LOC = "P43"  ; 
NET "RA<3>"  LOC = "P41"  ; 
NET "RA<4>"  LOC = "P40"  ; 
NET "RA<5>"  LOC = "P42"  ; 
NET "RA<6>"  LOC = "P46"  ; 
NET "RA<7>"  LOC = "P52"  ; 
NET "RA<8>"  LOC = "P54"  ; 
NET "RA<9>"  LOC = "P56"  ; 
NET "GA<22>"  LOC = "P61"  ;
NET "GA<23>"  LOC = "P60"  ;
NET "RnW_IOB"  LOC = "P59" | SLEW = SLOW  ;
NET "DBG<0>"  LOC = "P67"  ;
NET "DBG<1>"  LOC = "P68"  ;
NET "DBG<2>"  LOC = "P49"  ;
NET "DBG<3>"  LOC = "P39"  ;
NET "DBG<4>"  LOC = "P71"  ;
NET "DBG<5>"  LOC = "P1"  ;
